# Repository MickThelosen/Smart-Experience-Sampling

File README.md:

# Smart Experience Sampling

## Setup

The user manual specifies the steps are needed to setup the system

Button B2 starts the ranging process

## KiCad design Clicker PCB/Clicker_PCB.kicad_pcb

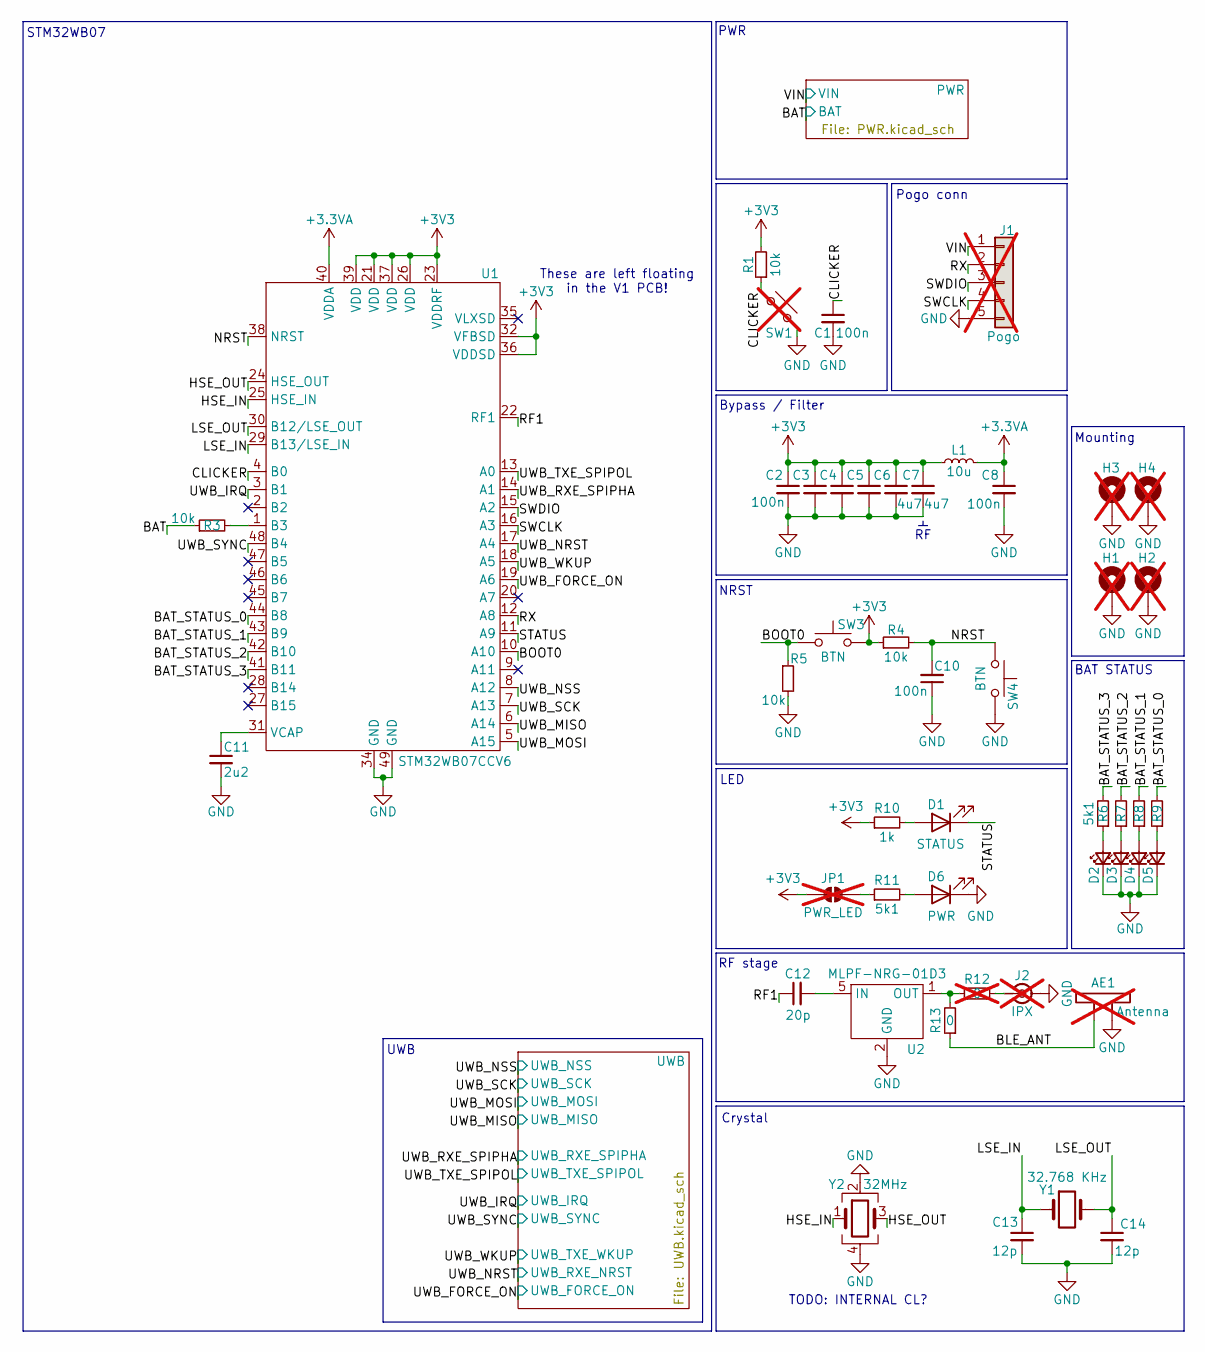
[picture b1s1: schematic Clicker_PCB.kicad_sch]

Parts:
AE1: Antenna; Texas_SWRA117D_2.4GHz_Right; not fitted
C1, C2, C3, C4, C5, C8, C10: 100n; C_0603_1608Metric; mouser 80-C0603C104M4RAUTO
C6, C7: 4u7; C_0603_1608Metric; mouser 963-JMK107BJ475MA-T
C11: 2u2; C_0603_1608Metric; mouser 187-CL10B225KP8NNNC
C12: 20p; C_0603_1608Metric; LCSC C1547
C13, C14: 12p; C_0603_1608Metric; LCSC C1547
D1: STATUS; LED_0603_1608Metric; mouser 710-150060BS75000
D2, D3, D4, D5: Green; LED_0603_1608Metric; mouser 710-150060GS75000
D6: PWR; LED_0603_1608Metric; mouser 710-150060RS75000
H1, H2, H3, H4: MountingHole_Pad; MountingHole_2.2mm_M2_Pad_Via; not fitted
J1: Pogo; PinHeader_1x05_P2.54mm_Vertical; not fitted
J2: IPX; U.FL_Molex_MCRF_73412-0110_Vertical; not fitted
JP1: PWR_LED; SolderJumper-2_P1.3mm_Open_TrianglePad1.0x1.5mm; not fitted
L1: 10u; L_0805_2012Metric; LCSC C139245
R1, R3, R4, R5: 10k; R_0603_1608Metric; mouser 71-CRCW060310K0FKED
R6, R7, R8, R9, R11: 5k1; R_0603_1608Metric; mouser 791-RMC1/16-512JTP
R10: 1k; R_0603_1608Metric; mouser 71-CRCW06031K00FKEE
R12: 0; R_0603_1608Metric; mouser 71-CRCW06030000Z0EI; not fitted
R13: 0; R_0603_1608Metric; mouser 71-CRCW06030000Z0EI
SW1: CLICKER; PinHeader_2x01_P2.54mm_Vertical; not fitted
SW3, SW4: BTN; SW_SPST_PTS810; LCSC C2681476
U1: STM32WB07CCV6; QFN-48-1EP_6x6mm_P0.4mm_EP4.3x4.3mm; mouser 511-STM32WB07CCV6TR
U2: MLPF-NRG-01D3; CSPG; mouser 511-MLPF-NRG-01D3
Y1: 32.768 KHz; Crystal_SMD_3215-2Pin_3.2x1.5mm; LCSC C32346
Y2: 32MHz; Crystal_SMD_3225-4Pin_3.2x2.5mm; LCSC C9006

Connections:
+3.3VA: C8.1, L1.2, U1.40 (VDDA)
+3V3: C2.1, C3.1, C4.1, C5.1, C6.1, C7.1, JP1.1 (A), L1.1, R1.2, R4.1, R10.1, SW3.2, U1.21 (VDD), U1.23 (VDDRF), U1.26 (VDD), U1.32 (VFBSD), U1.36 (VDDSD), U1.37 (VDD), U1.39 (VDD); also elsewhere on the board
/BAT: R3.1; also elsewhere on the board
/BAT_STATUS_0: R9.2, U1.44 (B8)
/BAT_STATUS_1: R8.2, U1.43 (B9)
/BAT_STATUS_2: R7.2, U1.42 (B10)
/BAT_STATUS_3: R6.2, U1.41 (B11)
/BLE_ANT: AE1.1, R13.1
/BOOT0: R5.1, SW3.1, U1.10 (A10)
/CLICKER: C1.1, R1.1, SW1.1, U1.4 (B0)
/HSE_IN: U1.25 (HSE_IN), Y2.1
/HSE_OUT: U1.24 (HSE_OUT), Y2.3
/LSE_IN: C13.1, U1.29 (B13/LSE_IN), Y1.1
/LSE_OUT: C14.1, U1.30 (B12/LSE_OUT), Y1.2
/NRST: C10.2, R4.2, SW4.1, U1.38 (NRST)
/RF1: C12.1, U1.22 (RF1)
/RX: J1.2, U1.12 (A8)
/STATUS: D1.1 (K), U1.11 (A9)
/SWCLK: J1.4, U1.16 (A3)
/SWDIO: J1.3, U1.15 (A2)
/UWB_FORCE_ON: U1.19 (A6); also elsewhere on the board
/UWB_IRQ: U1.3 (B1); also elsewhere on the board
/UWB_MISO: U1.6 (A14); also elsewhere on the board
/UWB_MOSI: U1.5 (A15); also elsewhere on the board
/UWB_NRST: U1.17 (A4); also elsewhere on the board
/UWB_NSS: U1.8 (A12); also elsewhere on the board
/UWB_RXE_SPIPHA: U1.14 (A1); also elsewhere on the board
/UWB_SCK: U1.7 (A13); also elsewhere on the board
/UWB_SYNC: U1.48 (B4); also elsewhere on the board
/UWB_TXE_SPIPOL: U1.13 (A0); also elsewhere on the board
/UWB_WKUP: U1.18 (A5); also elsewhere on the board
/VIN: J1.1; also elsewhere on the board
GND: AE1.2, C1.2, C2.2, C3.2, C4.2, C5.2, C6.2, C7.2, C8.2, C10.1, C11.2, C13.2, C14.2, D2.1 (K), D3.1 (K), D4.1 (K), D5.1 (K), D6.1 (K), H1.1, H2.1, H3.1, H4.1, J1.5, J2.2 (Ext), R5.2, SW1.2, SW4.2, U1.34 (GND), U1.49 (GND), U2.2 (GND), U2.3 (GND), U2.4 (GND), U2.6 (GND), Y2.2, Y2.4; also elsewhere on the board
unnamed: D1.2 (A), R10.2
unnamed: D2.2 (A), R6.1
unnamed: D3.2 (A), R7.1
unnamed: D4.2 (A), R8.1
unnamed: D5.2 (A), R9.1
unnamed: D6.2 (A), R11.2
unnamed: J2.1 (In), R12.2
unnamed: JP1.2 (B), R11.1
unnamed: R3.2, U1.1 (B3)
unnamed: C11.1, U1.31 (VCAP)
unnamed: C12.2, U2.5 (IN)
unnamed: R12.1, R13.2, U2.1 (OUT)

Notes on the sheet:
Pogo conn
TODO: INTERNAL CL?
BAT STATUS
STM32WB07
These are left floating in the V1 PCB!
LED
Crystal
UWB
PWR
NRST
RF stage
Mounting
Bypass / Filter

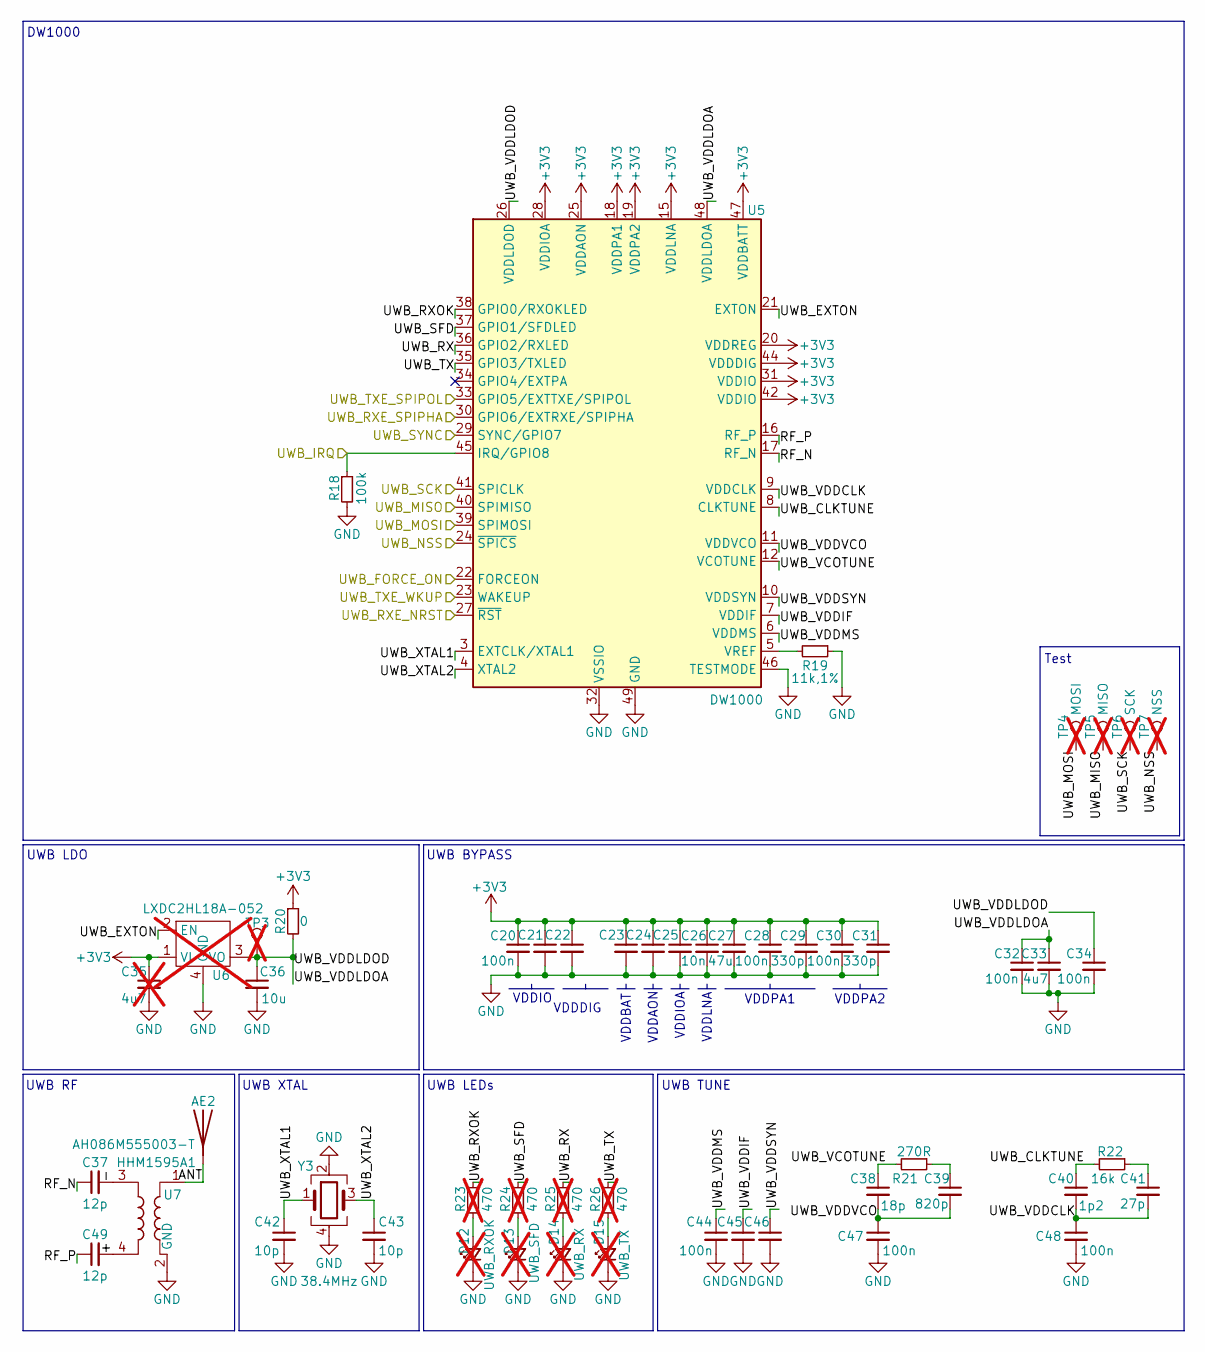
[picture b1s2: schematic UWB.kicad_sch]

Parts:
AE2: AH086M555003-T; AH086Mx; mouser 963-AH086M555003-T
C20, C21, C22, C23, C24, C25, C28, C30, C32, C34, C44, C45, C46, C47, C48: 100n; C_0603_1608Metric; LCSC C1547
C26: 10n; C_0603_1608Metric; LCSC C1547
C27: 47u; C_0603_1608Metric; LCSC C1547
C29, C31: 330p; C_0603_1608Metric; LCSC C1547
C33: 4u7; C_0603_1608Metric; LCSC C1547
C35: 4u7; C_0603_1608Metric; LCSC C1547; not fitted
C36: 10u; C_0603_1608Metric; LCSC C1547
C37, C49: 12p; C_0603_1608Metric; mouser 791-0603N120J500CT
C38: 18p; C_0603_1608Metric; LCSC C1547
C39: 820p; C_0603_1608Metric; LCSC C1547
C40: 1p2; C_0603_1608Metric; LCSC C1547
C41: 27p; C_0603_1608Metric; LCSC C1547
C42, C43: 10p; C_0603_1608Metric; LCSC C1547
D12: UWB_RXOK; LED_0603_1608Metric; mouser 710-150060GS75000; not fitted
D13: UWB_SFD; LED_0603_1608Metric; mouser 710-150060RS75000; not fitted
D14: UWB_RX; LED_0603_1608Metric; mouser 710-150060BS75000; not fitted
D15: UWB_TX; LED_0603_1608Metric; mouser 710-150060BS75000; not fitted
R18: 100k; R_0603_1608Metric; mouser 603-RT0603FRE13100KL
R19: 11k,1%; R_0603_1608Metric; mouser 603-RT0603DRD0711KL
R20: 0; R_0603_1608Metric; mouser 71-CRCW06030000Z0EI
R21: 270R; R_0603_1608Metric; mouser 755-ESR03EZPF2700
R22: 16k; R_0603_1608Metric; mouser 660-RK73B1JTTD163J
R23, R24, R25, R26: 470; R_0603_1608Metric; mouser 791-WR06X4700FTL; not fitted
TP3: UWB_LDO; TestPoint_Pad_D1.5mm; not fitted
TP4: MOSI; TestPoint_Keystone_5000-5004_Miniature; not fitted
TP5: MISO; TestPoint_Keystone_5000-5004_Miniature; not fitted
TP6: SCK; TestPoint_Keystone_5000-5004_Miniature; not fitted
TP7: NSS; TestPoint_Keystone_5000-5004_Miniature; not fitted
U5: DW1000; QFN-48-1EP_6x6mm_P0.4mm_EP4.2x4.2mm; mouser 772-DW1000-I-TR13
U6: LXDC2HL18A-052; LXDC2HL; mouser 81-LXDC2HL18A-052; not fitted
U7: HHM1595A1; mouser 810-HHM1595A1
Y3: 38.4MHz; Crystal_SMD_2520-4Pin_2.5x2.0mm; mouser 815-ABM1016538.4MT3

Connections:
+3V3: C20.1, C21.1, C22.1, C23.1, C24.1, C25.1, C26.1, C27.1, C28.1, C29.1, C30.1, C31.1, C35.1, R20.1, U5.15 (VDDLNA), U5.18 (VDDPA1), U5.19 (VDDPA2), U5.20 (VDDREG), U5.25 (VDDAON), U5.28 (VDDIOA), U5.31 (VDDIO), U5.42 (VDDIO), U5.44 (VDDDIG), U5.47 (VDDBATT), U6.1 (VI); also elsewhere on the board
/UWB/+: C49.2, U7.4
/UWB/-: C37.2, U7.3
/UWB/ANT: AE2.1 (A), U7.1
/UWB/RF_N: C37.1, U5.17 (RF_N)
/UWB/RF_P: C49.1, U5.16 (RF_P)
/UWB/UWB_CLKTUNE: C40.1, R22.2, U5.8 (CLKTUNE)
/UWB/UWB_EXTON: U5.21 (EXTON), U6.2 (EN)
/UWB/UWB_RX: R25.1, U5.36 (GPIO2/RXLED)
/UWB/UWB_RXOK: R23.1, U5.38 (GPIO0/RXOKLED)
/UWB/UWB_SFD: R24.1, U5.37 (GPIO1/SFDLED)
/UWB/UWB_TX: R26.1, U5.35 (GPIO3/TXLED)
/UWB/UWB_VCOTUNE: C38.1, R21.2, U5.12 (VCOTUNE)
/UWB/UWB_VDDCLK: C40.2, C41.2, C48.1, U5.9 (VDDCLK)
/UWB/UWB_VDDIF: C45.1, U5.7 (VDDIF)
/UWB/UWB_VDDLDOA: C32.1, C33.1, C34.1, C36.1, R20.2, TP3.1, U5.26 (VDDLDOD), U5.48 (VDDLDOA), U6.3 (VO)
/UWB/UWB_VDDMS: C44.1, U5.6 (VDDMS)
/UWB/UWB_VDDSYN: C46.1, U5.10 (VDDSYN)
/UWB/UWB_VDDVCO: C38.2, C39.2, C47.1, U5.11 (VDDVCO)
/UWB/UWB_XTAL1: C42.1, U5.3 (EXTCLK/XTAL1), Y3.1
/UWB/UWB_XTAL2: C43.1, U5.4 (XTAL2), Y3.3
/UWB_FORCE_ON: U5.22 (FORCEON); also elsewhere on the board
/UWB_IRQ: R18.1, U5.45 (IRQ/GPIO8); also elsewhere on the board
/UWB_MISO: TP5.1, U5.40 (SPIMISO); also elsewhere on the board
/UWB_MOSI: TP4.1, U5.39 (SPIMOSI); also elsewhere on the board
/UWB_NRST: U5.27 (~RST); also elsewhere on the board
/UWB_NSS: TP7.1, U5.24 (~SPICS); also elsewhere on the board
/UWB_RXE_SPIPHA: U5.30 (GPIO6/EXTRXE/SPIPHA); also elsewhere on the board
/UWB_SCK: TP6.1, U5.41 (SPICLK); also elsewhere on the board
/UWB_SYNC: U5.29 (SYNC/GPIO7); also elsewhere on the board
/UWB_TXE_SPIPOL: U5.33 (GPIO5/EXTTXE/SPIPOL); also elsewhere on the board
/UWB_WKUP: U5.23 (WAKEUP); also elsewhere on the board
GND: C20.2, C21.2, C22.2, C23.2, C24.2, C25.2, C26.2, C27.2, C28.2, C29.2, C30.2, C31.2, C32.2, C33.2, C34.2, C35.2, C36.2, C42.2, C43.2, C44.2, C45.2, C46.2, C47.2, C48.2, D12.1 (K), D13.1 (K), D14.1 (K), D15.1 (K), R18.2, R19.1, U5.32 (VSSIO), U5.43 (VSSIO), U5.46 (TESTMODE), U5.49 (GND), U6.4 (GND), U7.2 (GND), U7.5 (GND), Y3.2, Y3.4; also elsewhere on the board
unnamed: C39.1, R21.1
unnamed: C41.1, R22.1
unnamed: D12.2 (A), R23.2
unnamed: D13.2 (A), R24.2
unnamed: D14.2 (A), R25.2
unnamed: D15.2 (A), R26.2
unnamed: R19.2, U5.5 (VREF)

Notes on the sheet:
VDDIO
VDDBAT
VDDDIG
DW1000
VDDLNA
UWB RF
UWB TUNE
UWB XTAL
UWB LDO
UWB BYPASS
VDDAON
VDDIOA
Test
VDDPA2
VDDPA1
UWB LEDs

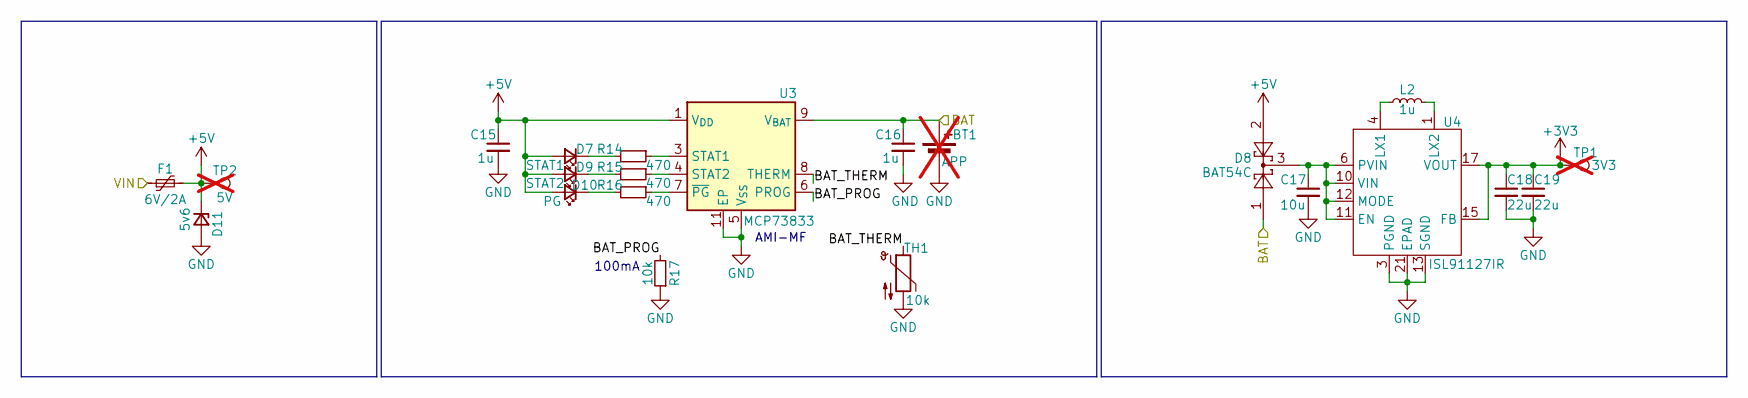
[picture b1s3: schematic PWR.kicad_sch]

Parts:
BT1: APP; PinHeader_1x02_P2.54mm_Vertical; not fitted
C15, C16: 1u; C_0603_1608Metric; mouser 963-MLAST168SB7105KT
C17: 10u; C_0603_1608Metric; mouser 187-CL10A106MQ8NNND
C18, C19: 22u; C_0603_1608Metric; mouser 187-CL10A226MP8NUNE
D7: STAT1; LED_0603_1608Metric; mouser 710-150060AS75000
D8: BAT54C; SOT-23; mouser 583-BAT54C
D9: STAT2; LED_0603_1608Metric; mouser 710-150060AS75000
D10: PG; LED_0603_1608Metric; mouser 710-150060RS75000
D11: 5v6; D_SOD-123; mouser 78-BZT52C5V6-E3-08
F1: 6V/2A; Fuse_1206_3216Metric; mouser 504-PTS18126V260
L2: 1u; L_0805_2012Metric; mouser 810-MLZ2012N1R0LT000
R14, R15, R16: 470; R_0603_1608Metric; LCSC C23186
R17: 10k; R_0603_1608Metric; LCSC C23186
TH1: 10k; R_0603_1608Metric; mouser 667-ERT-J1VR103J
TP1: 3V3; TestPoint_Pad_D1.5mm; not fitted
TP2: 5V; TestPoint_Pad_D1.5mm; not fitted
U3: MCP73833; DFN-10-1EP_3x3mm_P0.5mm_EP1.58x2.35mm; mouser 579-MCP73833T-AMI/MF
U4: ISL91127IR; QFN-20-1EP_4x4mm_P0.5mm_EP2.7x2.7mm_ThermalVias; mouser 968-ISL91127IRAZ-T

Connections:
+3V3: C18.1, C19.1, TP1.1, U4.15 (FB), U4.17 (VOUT), U4.18 (VOUT), U4.19 (VOUT), U4.20 (VOUT); also elsewhere on the board
+5V: C15.1, D7.2 (A), D8.2, D9.2 (A), D10.2 (A), D11.1 (K), F1.2, TP2.1, U3.1 (V_{DD}), U3.2 (V_{DD})
/BAT: BT1.1 (+), C16.1, D8.1, U3.9 (V_{BAT}), U3.10 (V_{BAT}); also elsewhere on the board
/PWR/BAT_PROG: R17.2, U3.6 (PROG)
/PWR/BAT_THERM: TH1.1, U3.8 (THERM)
/VIN: F1.1; also elsewhere on the board
GND: BT1.2 (-), C15.2, C16.2, C17.2, C18.2, C19.2, D11.2 (A), R17.1, TH1.2, U3.5 (V_{SS}), U3.11 (EP), U4.3 (PGND), U4.13 (SGND), U4.14 (SGND), U4.21 (EPAD); also elsewhere on the board
unnamed: D7.1 (K), R14.2
unnamed: D9.1 (K), R15.2
unnamed: D10.1 (K), R16.2
unnamed: L2.1, U4.4 (LX1), U4.5 (LX1)
unnamed: L2.2, U4.1 (LX2), U4.2 (LX2)
unnamed: R14.1, U3.3 (STAT1)
unnamed: R15.1, U3.4 (STAT2)
unnamed: R16.1, U3.7 (~PG)
unnamed: C17.1, D8.3, U4.6 (PVIN), U4.7 (PVIN), U4.8 (PVIN), U4.9 (PVIN), U4.10 (VIN), U4.11 (EN), U4.12 (MODE)

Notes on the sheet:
AMI-MF
100mA

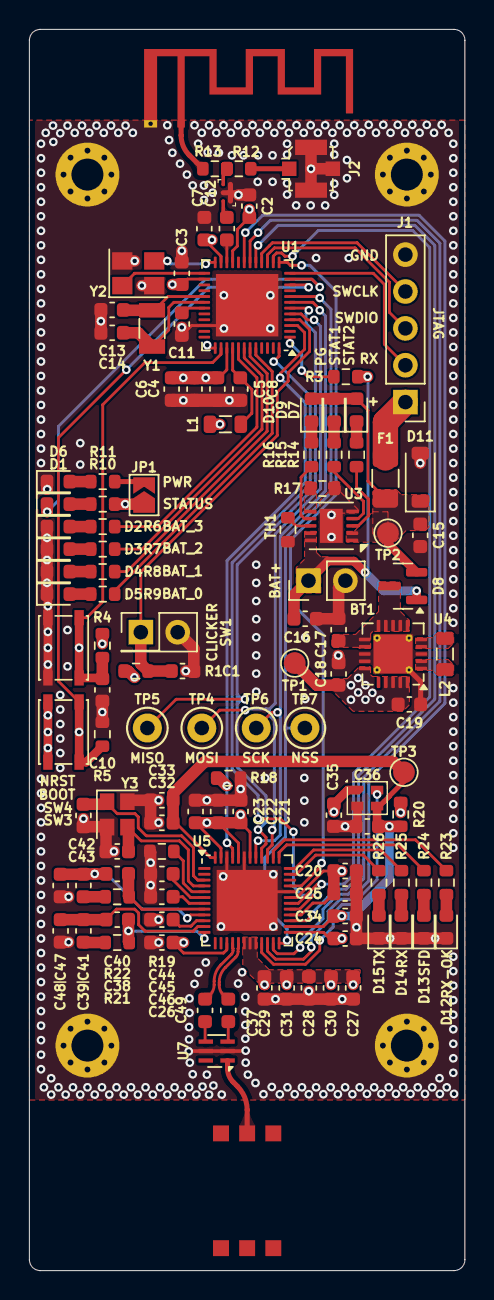
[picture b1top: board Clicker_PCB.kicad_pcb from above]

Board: 4 copper layers, 30.0 x 85.5 mm, 122 parts (0 on the bottom side), 84 nets.

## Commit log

2025-01-19 All files from the SES project for future use.
2025-01-19 Added README.md
2025-01-21 Working Demo Code
2025-01-27 Updated PCB, Beacon-Visualizer, Code Explaination, User Manual, and added back- & frontend.
